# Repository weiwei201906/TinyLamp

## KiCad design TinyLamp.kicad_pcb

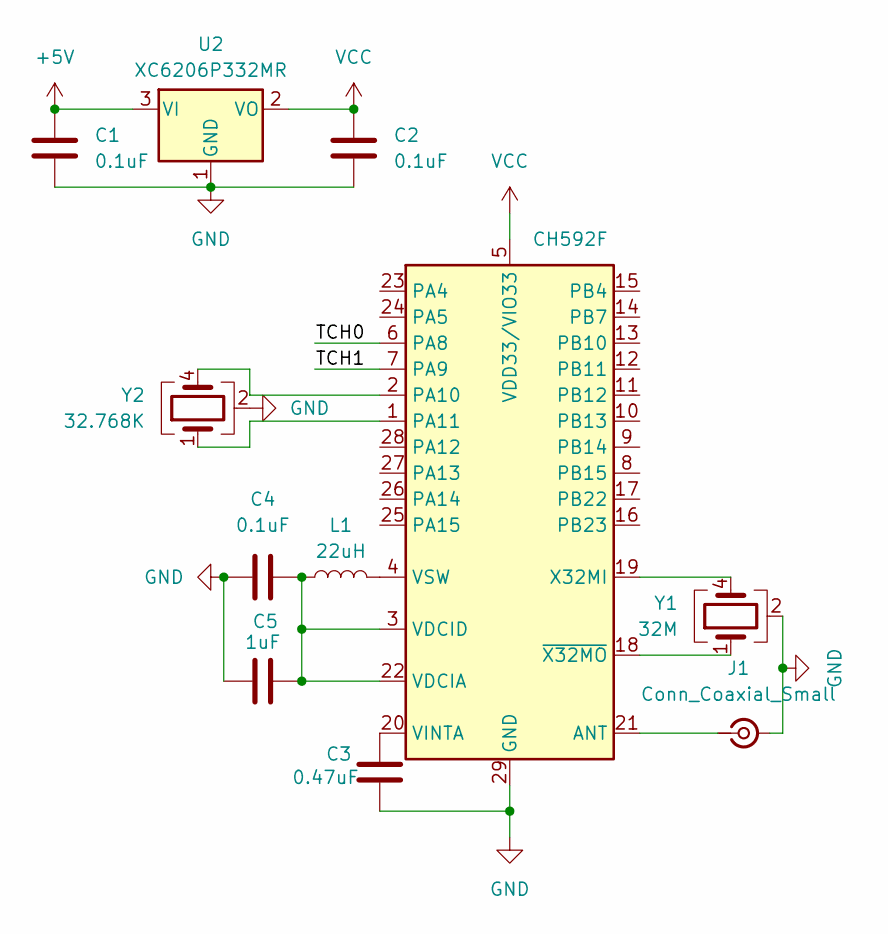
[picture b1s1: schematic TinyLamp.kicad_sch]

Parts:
C1, C2, C4: 0.1uF; C_0402_1005Metric
C3: 0.47uF; C_0402_1005Metric
C5: 1uF; C_0402_1005Metric
J1: Conn_Coaxial_Small; U.FL_Molex_MCRF_73412-0110_Vertical
L1: 22uH; L_0402_1005Metric
U1: CH592F; WQFN-28-1EP_4x4mm_P0.4mm_EP2.7x2.7mm
U2: XC6206P332MR; SOT-23-3
Y1: 32M; Crystal_SMD_3225-4Pin_3.2x2.5mm
Y2: 32.768K; Crystal_SMD_1210-4Pin_1.2x1.0mm

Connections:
+5V: C1.1, U2.3 (VI)
/TCH0: U1.6 (PA8)
/TCH1: U1.7 (PA9)
GND: C1.2, C2.2, C3.2, C4.1, C5.1, J1.2 (Ext), U1.29 (GND), U2.1 (GND), Y1.2 (G), Y1.3 (G), Y2.2 (G), Y2.3 (G)
unnamed: J1.1 (In), U1.21 (ANT)
unnamed: U1.2 (PA10), Y2.4
unnamed: U1.1 (PA11), Y2.1
unnamed: C4.2, C5.2, L1.1, U1.3 (VDCID), U1.22 (VDCIA)
unnamed: C3.1, U1.20 (VINTA)
unnamed: L1.2, U1.4 (VSW)
unnamed: U1.19 (X32MI), Y1.4
unnamed: U1.18 (~X32MO), Y1.1
VCC: C2.1, U1.5 (VDD33/VIO33), U2.2 (VO)

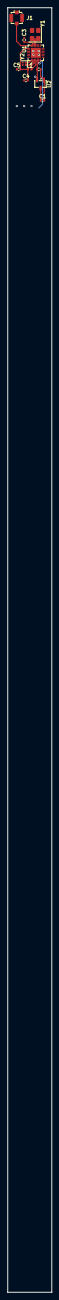
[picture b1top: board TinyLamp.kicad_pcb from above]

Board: 2 copper layers, 12.0 x 350.0 mm, 11 parts (0 on the bottom side), 11 nets.

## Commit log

2026-05-17 Core
2026-05-22 Touch
